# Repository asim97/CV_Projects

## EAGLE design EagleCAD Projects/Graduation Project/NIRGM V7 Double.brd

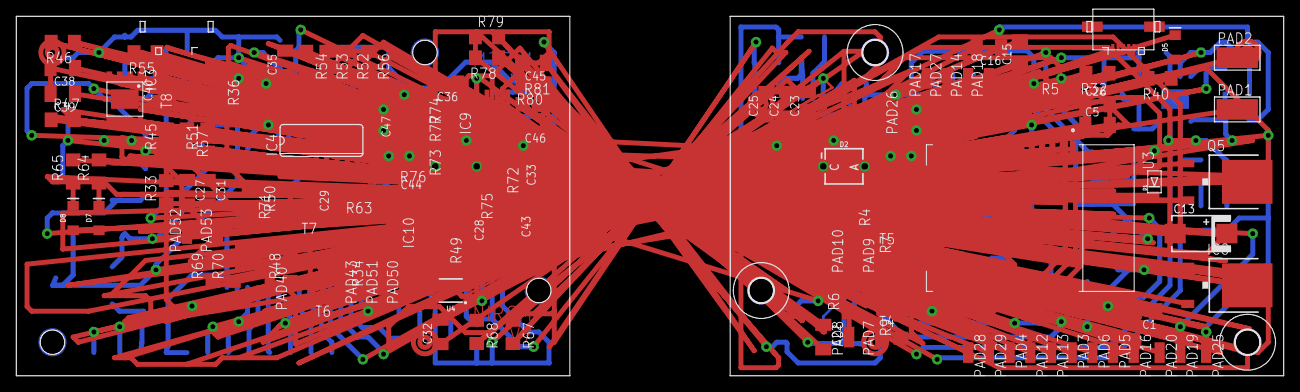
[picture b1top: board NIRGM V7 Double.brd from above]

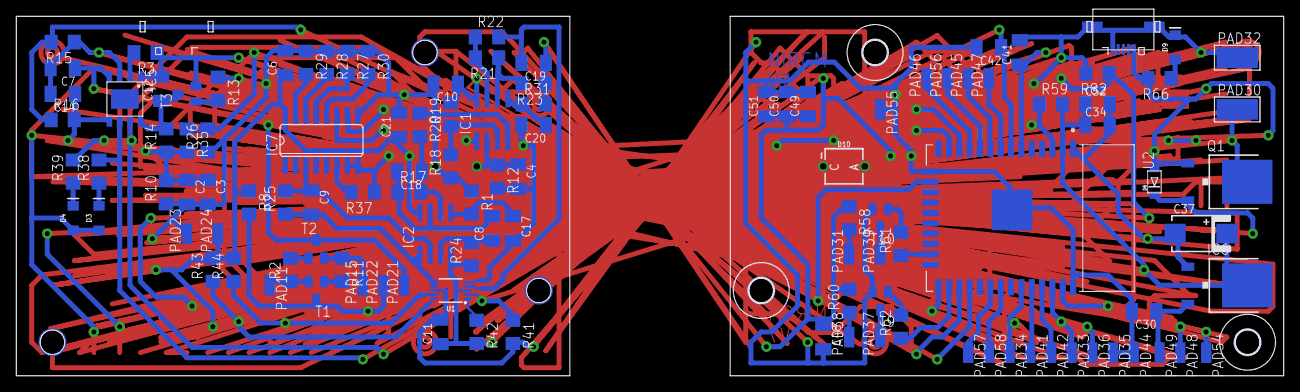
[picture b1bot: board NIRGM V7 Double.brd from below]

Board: 2 copper layers, 155.6 x 44.1 mm, 236 parts (118 on the bottom side), 126 nets.

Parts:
C1, C3, C7, C8, C12, C14, C17, C24, C25, C28, C30, C31, C38, C39, C40, C43, C50, C51: 10uf; C1206K
C2, C5, C6, C9, C10, C15, C16, C18, C21, C22, C23, C26, C27, C29, C34, C35, C36, C41, C42, C44, C47, C48, C49, C52: 100nf; C1206K
C4, C33: 5.7pf; C1206K
C11, C32: 1uf; C1206K
C13, C37: 220uf; 7343/T
C19, C45: 100nF; C1206K
C20, C46: 1uF; C1206K
D1, D6: SOD4007; SOD-123FL
D2, D10: BPW34
D3, D7: GREEN; LED-1206
D4, D5, D8, D9: RED; LED-1206
H1, H2, H3, H4, H5, H6: MOUNT-HOLE3.0; 3,0
IC1, IC2, IC9, IC10: MCP602SN; SO08
IC3, IC5: TP4056; SOP-8
IC4, IC7: 4051D; SO16
IC6, IC8: 3.3v; TO252
PAD1, PAD2, PAD30, PAD32: 5-2,5
PAD3, PAD4, PAD5, PAD6, PAD7, PAD8, PAD9, PAD10, PAD11, PAD12, PAD13, PAD14, PAD15, PAD16, PAD17, PAD18, PAD19, PAD20, PAD21, PAD22, PAD23, PAD24, PAD25, PAD26, PAD27, PAD28, PAD29, PAD31, PAD33, PAD34, PAD35, PAD36, PAD37, PAD38, PAD39, PAD40, PAD41, PAD42, PAD43, PAD44, PAD45, PAD46, PAD47, PAD48, PAD49, PAD50, PAD51, PAD52, PAD53, PAD54, PAD55, PAD56, PAD57, PAD58: SMD1,27-2,54
Q1, Q5: ME12P04; TO252
R1, R17, R18, R19, R73, R74, R75, R76: 100k; R1206
R2, R8, R10, R11, R14, R20, R24, R29, R33, R34, R37, R41, R42, R43, R44, R45, R48, R49, R54, R63, R67, R68, R69, R70, R71, R77: 10k; R1206
R3, R55: 2.2k; R1206
R4, R6, R58, R60: 20R; R1206
R5, R28, R32, R53, R59, R82: 4.7k; R1206
R7, R9, R13, R23, R27, R36, R38, R39, R40, R52, R61, R62, R64, R65, R66, R80: 1k; R1206
R12, R72: 1M; R1206
R15, R16, R26, R30, R35, R46, R47, R51, R56, R57: 47k; R1206
R21, R78: 57k; R1206
R22, R79: 200k; R1206
R25, R50: 220k; R1206
R31, R81: 2.2M; R1206
T1, T2, T3, T4, T5, T6, T7, T8, T9, T10: BC850; SOT23
U1, U4: ADS1015; MSOP10
U2, U3: ESP32-WROOM-32D; MODULE_ESP32-WROOM-32D
U$1, U$2: MICRO-USB; 47589-0001

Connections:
3.3V: C5.1, C6.1, C10.1, C11.2, C13.+, C21.1, C22.1, C23.1, C24.1, C25.1, C26.1, IC1.8, IC2.8, IC7.16, IC8.3, PAD6.1, PAD24.1, R4.1, R5.2, R6.2, R8.1, R19.2, R41.2, R43.2, R44.2, U1.8, U3.2
3.3V1: C32.2, C34.1, C35.1, C36.1, C37.+, C47.1, C48.1, C49.1, C50.1, C51.1, C52.1, IC4.16, IC6.3, IC9.8, IC10.8, PAD36.1, PAD53.1, R58.1, R59.2, R60.2, R67.2, R69.2, R70.2, R71.1, R74.2, U2.2, U4.8
ADS_COMP: R41.1, U1.2, U3.16
ADS_COMP1: R67.1, U2.16, U4.2
CHARGED_LOW: IC5.6, R38.2, U3.28
CHARGED_LOW1: IC3.6, R64.2, U2.28
CHARGE_DISABLE: R13.1, R32.1, U3.37
CHARGE_DISABLE1: R36.1, R82.1, U2.37
CHARGE_E: C12.1, IC5.8, R14.2, T3.3
CHARGE_E1: C40.1, IC3.8, R45.2, T8.3
CHARGING_LOW: IC5.7, R39.2, U3.27
CHARGING_LOW1: IC3.7, R65.2, U2.27
CHP_EN: PAD21.1, R5.1, T2.3, U3.3
CHP_EN1: PAD50.1, R59.1, T7.3, U2.3
CH_RX: PAD12.1, U3.34
CH_RX1: PAD41.1, U2.34
CH_TX: PAD13.1, U3.35
CH_TX1: PAD42.1, U2.35
DTR: PAD11.1, R2.1, T1.2
DTR1: PAD40.1, R48.1, T6.2
EN_IR1: R9.1, U3.26
EN_IR2: R7.1, U3.23
EN_IR3: R62.1, U2.26
EN_IR4: R61.1, U2.23
GND: C1.2, C2.2, C3.2, C5.2, C6.2, C7.2, C10.2, C11.1, C12.2, C13.-, C14.2, C15.2, C16.2, C19.1, C21.2, C22.2, C23.2, C24.2, C25.2, C26.2, D2.P$1, D5.C, IC1.4, IC2.4, IC5.1, IC5.3, IC7.7, IC7.8, IC7.9, IC8.1, PAD2.1, PAD5.1, PAD16.1, PAD23.1, PAD26.1, R1.1, R3.1, R10.1, R15.1, R18.1, R20.1, R23.1, R24.1, R26.1, R27.1, R28.1, R29.1, R30.1, R31.2, R32.2, R37.1, R42.2, T3.2, T4.2, T5.2, U1.3, U3.1, U3.15, U3.38, U3.39, U$1.5
GND1: C27.2, C30.2, C31.2, C32.1, C34.2, C35.2, C36.2, C37.-, C38.2, C39.2, C40.2, C41.2, C42.2, C45.1, C47.2, C48.2, C49.2, C50.2, C51.2, C52.2, D9.C, D10.P$1, IC3.1, IC3.3, IC4.7, IC4.8, IC4.9, IC6.1, IC9.4, IC10.4, PAD32.1, PAD35.1, PAD44.1, PAD52.1, PAD55.1, R33.1, R46.1, R49.1, R51.1, R52.1, R53.1, R54.1, R55.1, R56.1, R63.1, R68.2, R73.1, R75.1, R77.1, R80.1, R81.2, R82.2, T8.2, T9.2, T10.2, U2.1, U2.15, U2.38, U2.39, U4.3, U$2.5
IO0: PAD22.1, R8.2, T1.3, U3.25
IO1: PAD47.1, U2.8
IO2: PAD45.1, U2.9
IO3: PAD51.1, R71.2, T6.3, U2.25
IO4: PAD46.1, U2.11
IO5: PAD58.1, U2.31
IO6: PAD57.1, U2.30
IO7: PAD56.1, U2.10
IO18: PAD28.1, U3.30
IO19: PAD29.1, U3.31
IO25: PAD27.1, U3.10
IO26: PAD17.1, U3.11
IO32: PAD18.1, U3.8
IO33: PAD14.1, U3.9
IR1_LED_ANODE: PAD8.1, R6.1
IR1_LED_ANODE1: PAD38.1, R60.1
IR1_LED_CATHODE: PAD7.1, T4.3
IR1_LED_CATHODE1: PAD37.1, T9.3
IR2_LED_ANODE: PAD10.1, R4.2
IR2_LED_ANODE1: PAD31.1, R58.2
IR2_LED_CATHODE: PAD9.1, T5.3
IR2_LED_CATHODE1: PAD39.1, T10.3
unnamed: D5.A, R40.1
unnamed: D4.C, R39.1
unnamed: R7.2, T5.1
unnamed: D3.C, R38.1
unnamed: R11.2, T1.1
unnamed: C17.1, IC2.5, R1.2
unnamed: C4.1, D2.P$2, IC1.2, R12.1
unnamed: R9.2, T4.1
unnamed: R42.1, U1.1
unnamed: IC1.3, R18.2, R19.1
unnamed: IC7.6, R37.2
unnamed: C8.2, C18.2, IC2.7, R17.1
unnamed: R13.2, T3.1
unnamed: C18.1, IC2.6, R17.2, R20.2
unnamed: IC1.6, R21.1, R23.2
unnamed: C20.1, IC1.5, R31.1
unnamed: IC1.7, R21.2, R22.1
unnamed: R2.2, T2.1
unnamed: R36.2, T8.1
unnamed: R34.2, T6.1
unnamed: R48.2, T7.1
unnamed: C28.1, IC10.3, R49.2
unnamed: C29.1, IC4.3, IC10.2, R50.2
unnamed: IC4.13, R52.2
unnamed: IC4.14, R53.2
unnamed: IC4.15, R54.2
unnamed: C8.1, IC2.3, R24.2
unnamed: IC4.12, R56.2
unnamed: IC4.6, R63.2
unnamed: D9.A, R66.1
unnamed: R68.1, U4.1
unnamed: R62.2, T9.1
unnamed: R61.2, T10.1
unnamed: C33.1, D10.P$2, IC9.2, R72.1
unnamed: IC9.3, R73.2, R74.1
unnamed: D8.C, R65.1
unnamed: C9.1, IC2.2, IC7.3, R25.2
unnamed: IC7.13, R27.2
unnamed: IC7.14, R28.2
unnamed: IC7.15, R29.2
unnamed: IC7.12, R30.2
unnamed: D7.C, R64.1
unnamed: C43.1, IC10.5, R75.2
unnamed: C28.2, C44.2, IC10.7, R76.1
unnamed: C44.1, IC10.6, R76.2, R77.2
unnamed: IC9.6, R78.1, R80.2
unnamed: C46.1, IC9.5, R81.1
unnamed: IC9.7, R78.2, R79.1
PHOTODIODE_ADC: C4.2, C17.2, C20.2, IC1.1, R12.2, U1.5
PHOTODIODE_ADC1: C33.2, C43.2, C46.2, IC9.1, R72.2, U4.5
PPG_SIGNAL_1_ADC: C9.2, IC2.1, R25.1, U1.6, U1.7
PPG_SIGNAL_1_ADC1: C29.2, IC10.1, R50.1, U4.6, U4.7
PPG_SIGNAL_2_ADC: C19.2, R22.2, U1.4
PPG_SIGNAL_2_ADC1: C45.2, R79.2, U4.4
PPG_SIGNAL_GAIN_A: IC7.11, U3.13
PPG_SIGNAL_GAIN_A1: IC4.11, U2.13
PPG_SIGNAL_GAIN_B: IC7.10, U3.12
PPG_SIGNAL_GAIN_B1: IC4.10, U2.12
RTS: PAD15.1, R11.1, T2.2
RTS1: PAD43.1, R34.1, T7.2
R_PROG: IC5.2, R3.2
R_PROG1: IC3.2, R55.2
SCL: PAD3.1, R43.1, U1.10, U3.36
SCL1: PAD33.1, R69.1, U2.36, U4.10
SDA: PAD4.1, R44.1, U1.9, U3.33
SDA1: PAD34.1, R70.1, U2.33, U4.9
VIN: C1.1, IC8.2, PAD20.1
VIN1: C30.1, IC6.2, PAD49.1
VIN_SW: D1.C, PAD19.1, Q5.2
VIN_SW1: D6.C, PAD48.1, Q1.2
V_BATT: C14.1, IC5.5, PAD1.1, Q5.3, R16.2
V_BATT1: C39.1, IC3.5, PAD30.1, Q1.3, R47.2
V_BATT_ADC: C16.1, R15.2, R16.1, U3.7
V_BATT_ADC1: C42.1, R46.2, R47.1, U2.7
V_USB: C2.1, C3.1, C7.1, D1.A, D3.A, D4.A, IC5.4, PAD25.1, Q5.1, R10.2, R14.1, R35.2, R40.2, U$1.1
V_USB1: C27.1, C31.1, C38.1, D6.A, D7.A, D8.A, IC3.4, PAD54.1, Q1.1, R33.2, R45.1, R57.2, R66.2, U$2.1
V_USB_ADC: C15.1, R26.2, R35.1, U3.6
V_USB_ADC1: C41.1, R51.2, R57.1, U2.6

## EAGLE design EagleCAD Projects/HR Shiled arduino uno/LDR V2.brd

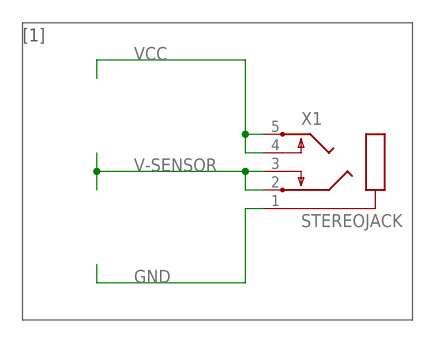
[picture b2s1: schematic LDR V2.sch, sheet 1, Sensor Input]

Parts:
X1: STEREOJACK; STX3100

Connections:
GND: X1.1; also elsewhere on the board
V-SENSOR: X1.2, X1.3; also elsewhere on the board
VCC: X1.4, X1.5; also elsewhere on the board

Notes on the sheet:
[1]

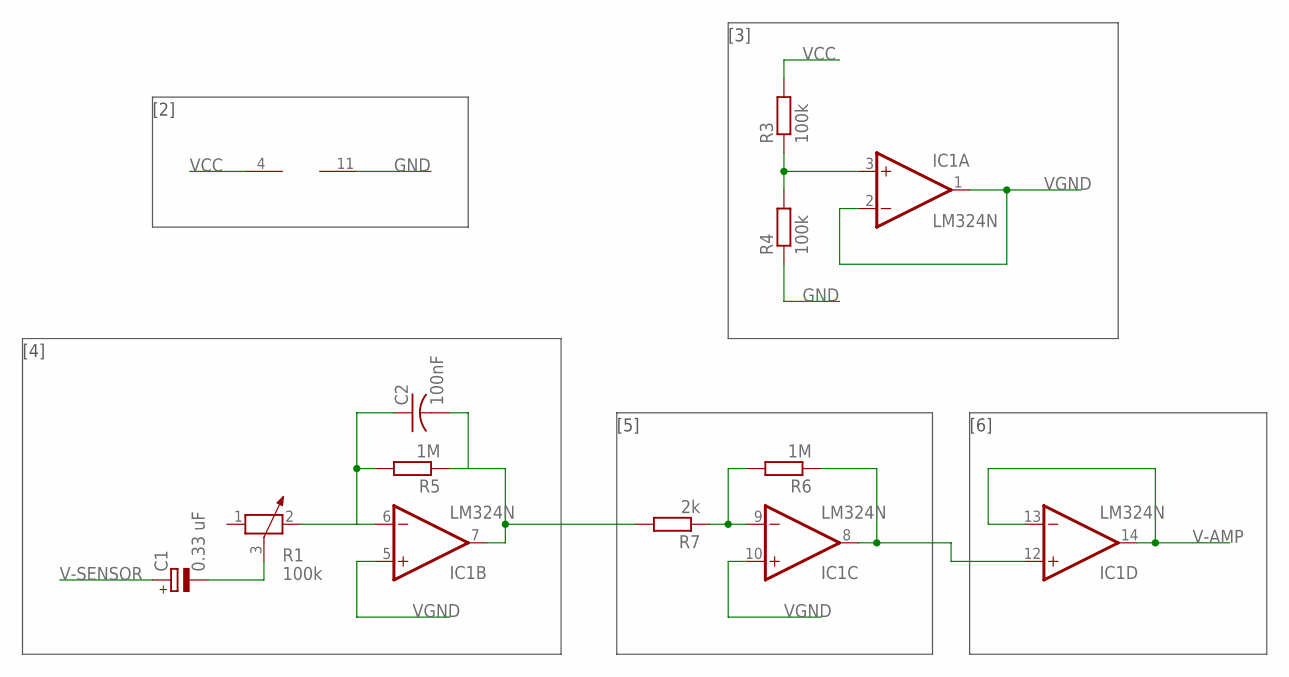
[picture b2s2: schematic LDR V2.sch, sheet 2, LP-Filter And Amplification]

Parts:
C1: 0.33 uF; E1,8-4
C2: 100nF; C025-025X050
IC1: LM324N; DIL14
R1: 100k; PT-10
R3, R4: 100k; 0207/7
R5, R6: 1M; 0207/7
R7: 2k; 0207/7

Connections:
GND: IC1.11 (V-), R4.1; also elsewhere on the board
unnamed: C1.-, R1.3
unnamed: C2.1, IC1.6 (-IN), R1.2, R5.2
unnamed: IC1.3 (+IN), R3.1, R4.2
unnamed: C2.2, IC1.7 (OUT), R5.1, R7.2
unnamed: IC1.9 (-IN), R6.2, R7.1
unnamed: IC1.8 (OUT), IC1.12 (+IN), R6.1
V-AMP: IC1.13 (-IN), IC1.14 (OUT); also elsewhere on the board
V-SENSOR: C1.+; also elsewhere on the board
VCC: IC1.4 (V+), R3.2; also elsewhere on the board
VGND: IC1.1 (OUT), IC1.2 (-IN), IC1.5 (+IN), IC1.10 (+IN)

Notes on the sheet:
[3]
[2]
[4]
[5]
[6]

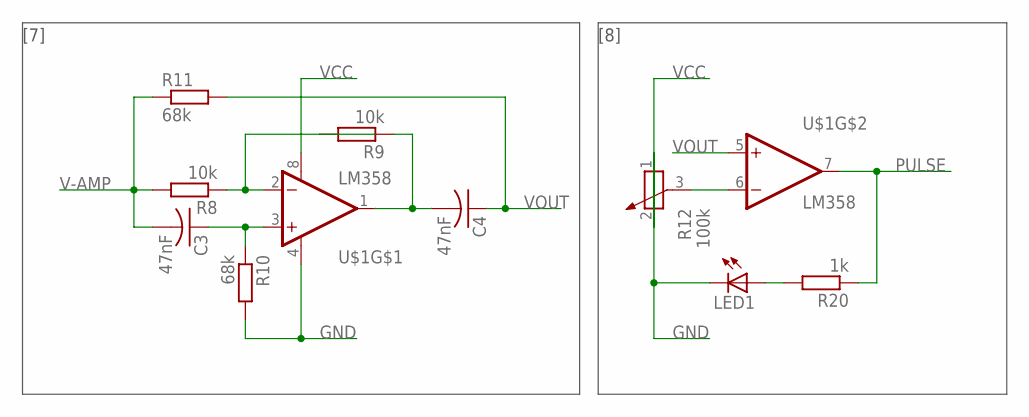
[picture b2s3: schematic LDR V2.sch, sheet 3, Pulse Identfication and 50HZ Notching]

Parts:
C3, C4: 47nF; C025-025X050
LED1: LED5MM
R8, R9: 10k; 0207/7
R10, R11: 68k; 0207/7
R12: 100k; PT-10
R20: 1k; 0207/7
U$1: LM358; DIP08

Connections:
GND: LED1.K (C), R10.2, R12.1, U$1.4 (V-); also elsewhere on the board
unnamed: R8.1, R9.2, U$1.2 (-IN)
unnamed: C3.1, R10.1, U$1.3 (+IN)
unnamed: R12.3, U$1.6 (-IN)
unnamed: C4.2, R9.1, U$1.1 (OUT)
unnamed: LED1.A, R20.2
PULSE: R20.1, U$1.7 (OUT); also elsewhere on the board
V-AMP: C3.2, R8.2, R11.1; also elsewhere on the board
VCC: R12.2, U$1.8 (V+); also elsewhere on the board
VOUT: C4.1, R11.2, U$1.5 (+IN); also elsewhere on the board

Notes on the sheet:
[7]
[8]

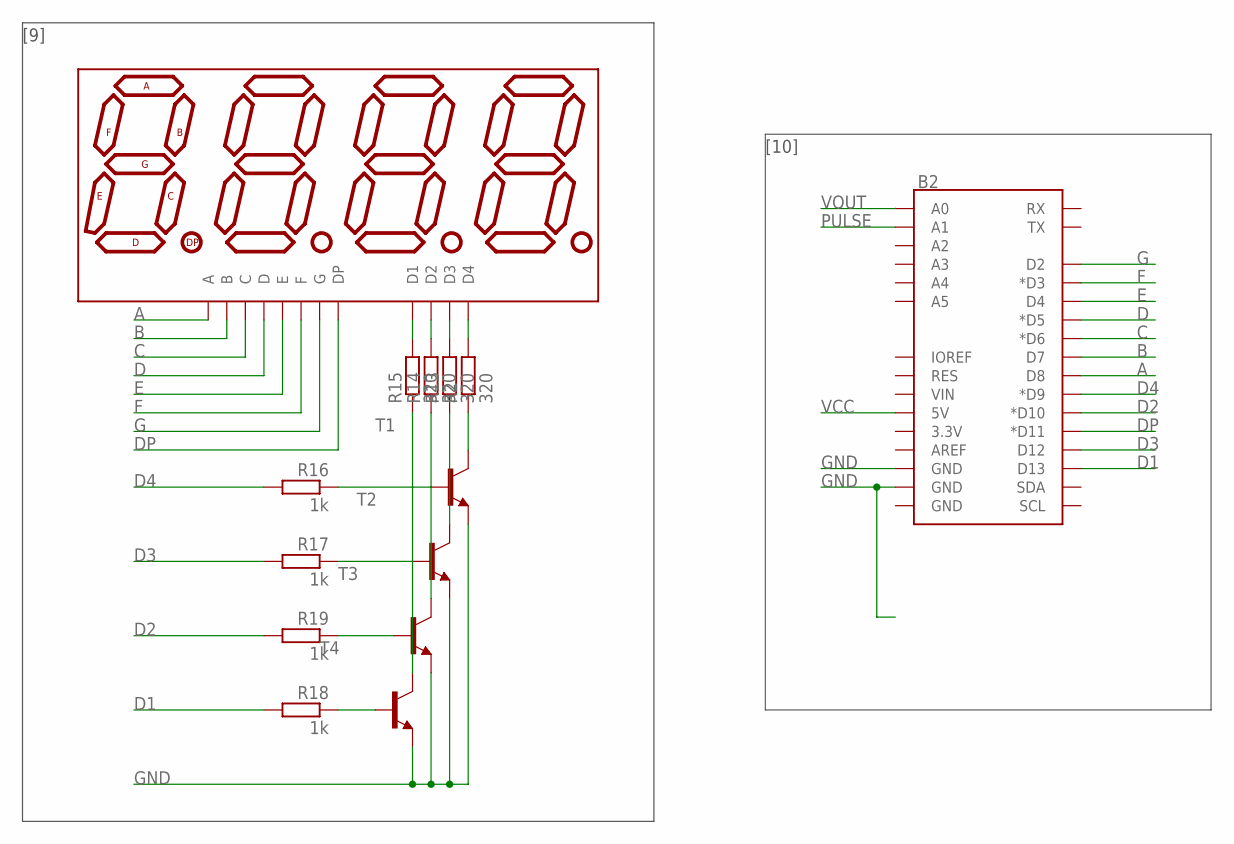
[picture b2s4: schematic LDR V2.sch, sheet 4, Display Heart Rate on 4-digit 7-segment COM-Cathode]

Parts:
B2: ARDUINO_UNO_R3_SHIELDUNO_R3_SHIELD_LOCK; UNO_R3_SHIELD_LOCK
DISP2: ATA8041AB; 7-SEGMENT-4DIGIT-20MM
R2, R13, R14, R15: 320; 0207/7
R16, R17, R18, R19: 1k; 0207/7
T1, T2, T3, T4: 2N2222-NPN-TO92-EBC; TO92-EBC

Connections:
1: DISP2.12 (D1), R15.2
2: DISP2.9 (D2), R14.2
3: DISP2.8 (D3), R13.2
4: DISP2.6 (D4), R2.2
A: B2.D8, DISP2.11 (A)
B: B2.D7, DISP2.7 (B)
C: B2.D6 (*D6), DISP2.4 (C)
D: B2.D5 (*D5), DISP2.2 (D)
D1: B2.D13, R18.2
D2: B2.D10 (*D10), R19.2
D3: B2.D12, R17.2
D4: B2.D9 (*D9), R16.2
DP: B2.D11 (*D11), DISP2.3 (DP)
E: B2.D4, DISP2.1 (E)
F: B2.D3 (*D3), DISP2.10 (F)
G: B2.D2, DISP2.5 (G)
GND: B2.GND@1 (GND), B2.GND@2 (GND), T1.E, T2.E, T3.E, T4.E; also elsewhere on the board
unnamed: R2.1, T1.C
unnamed: R18.1, T4.B
unnamed: R19.1, T3.B
unnamed: R17.1, T2.B
unnamed: R16.1, T1.B
unnamed: R13.1, T2.C
unnamed: R14.1, T3.C
unnamed: R15.1, T4.C
PULSE: B2.A1; also elsewhere on the board
VCC: B2.5V; also elsewhere on the board
VOUT: B2.A0; also elsewhere on the board

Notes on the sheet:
[9]
[10]

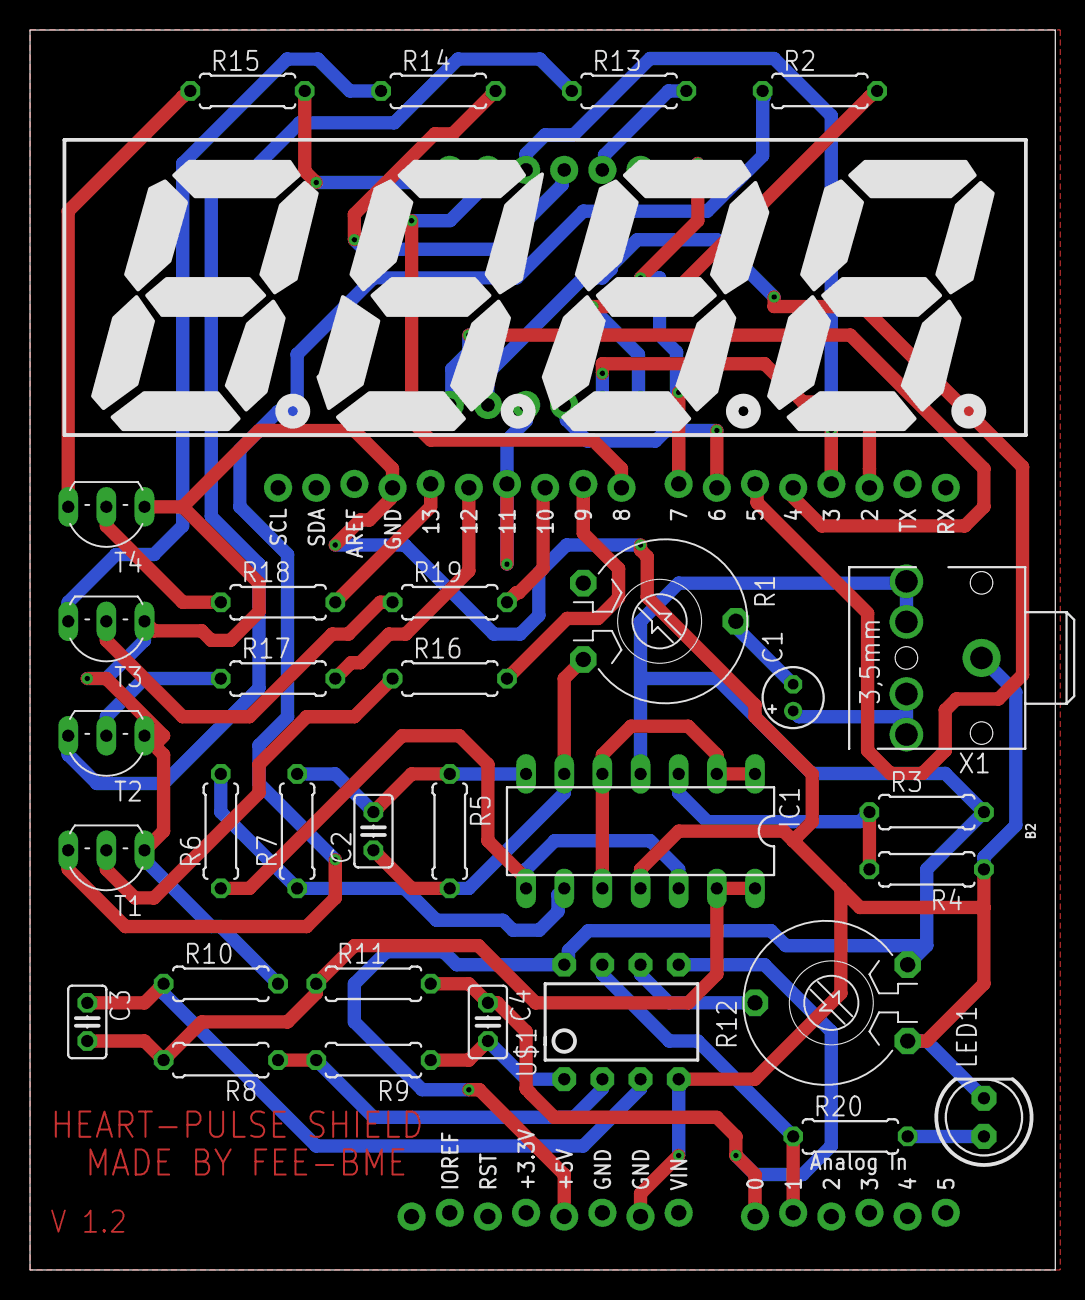
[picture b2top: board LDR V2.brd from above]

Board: 2 copper layers, 68.2 x 82.5 mm, 34 parts (0 on the bottom side), 42 nets.

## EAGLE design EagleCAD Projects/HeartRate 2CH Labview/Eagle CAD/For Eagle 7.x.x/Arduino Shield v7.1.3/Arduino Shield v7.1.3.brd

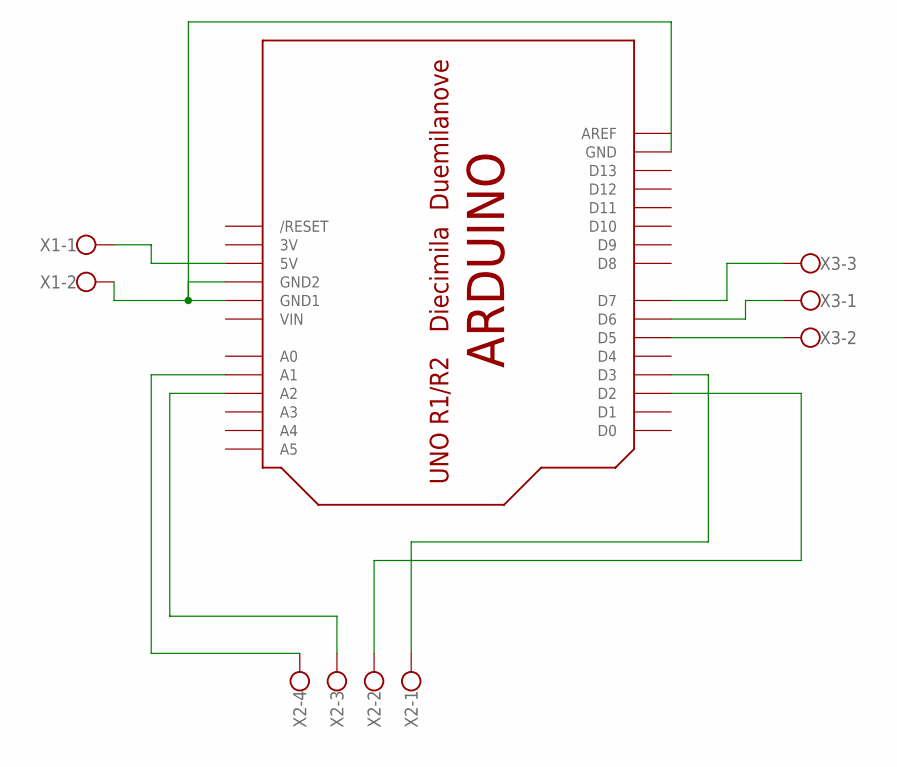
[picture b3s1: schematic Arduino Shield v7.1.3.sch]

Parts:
U$1: ARDUINOUNO; ARDUINO
X1: W237-102
X2: W237-4
X3: W237-103

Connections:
3V: U$1.3V
GND: U$1.GND, U$1.GND1, U$1.GND2, X1.2
unnamed: U$1.A1, X2.4
unnamed: U$1.A2, X2.3
unnamed: U$1.D3, X2.1
unnamed: U$1.D5, X3.2
unnamed: U$1.D6, X3.1
unnamed: U$1.D7, X3.3
unnamed: U$1.D2, X2.2
unnamed: U$1.5V, X1.1
VIN: U$1.VIN

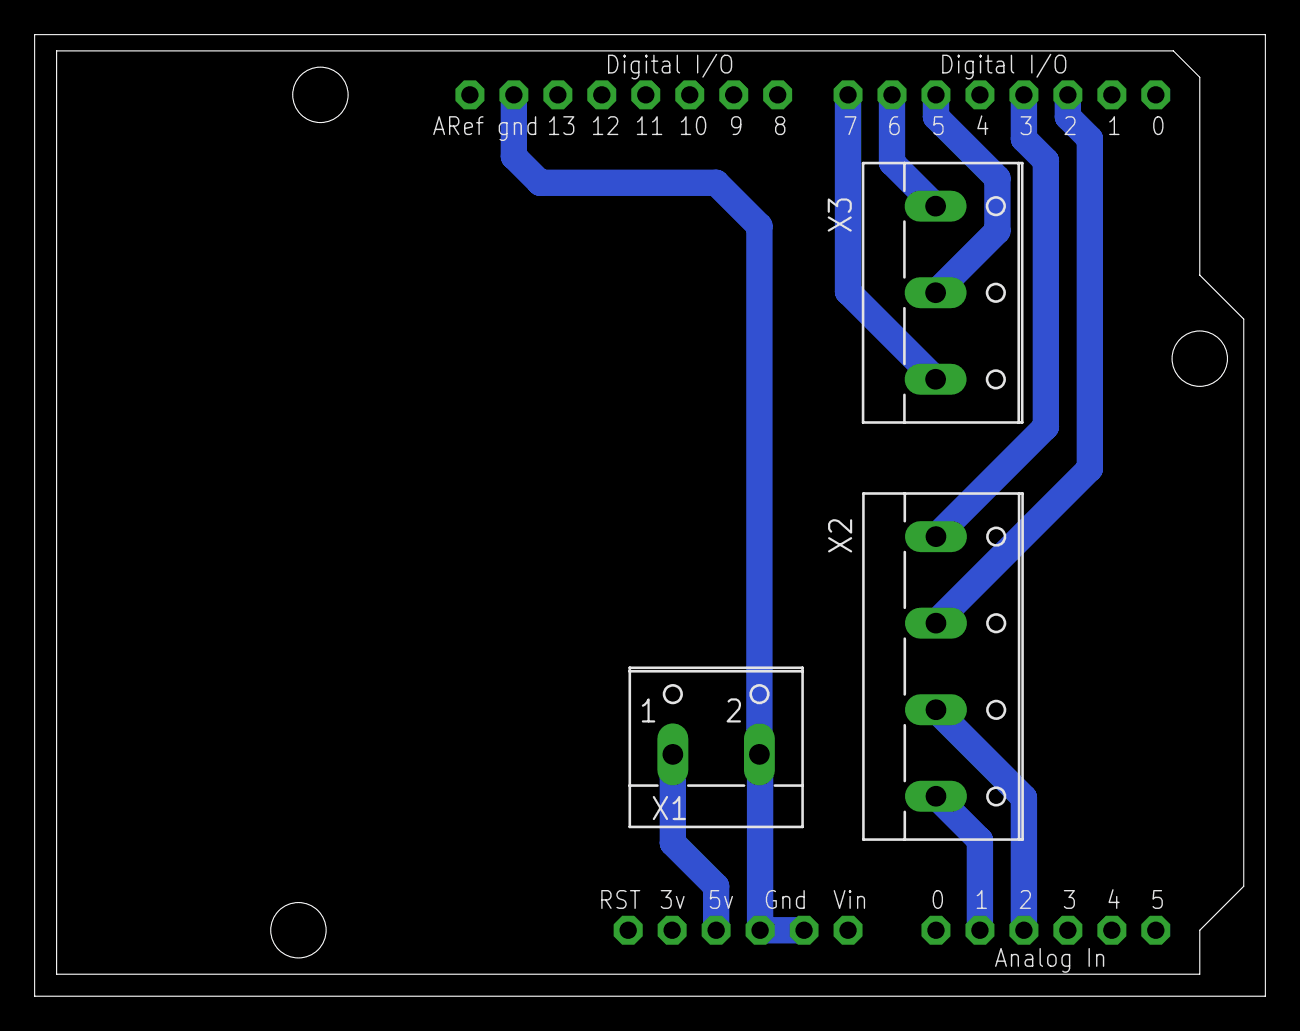
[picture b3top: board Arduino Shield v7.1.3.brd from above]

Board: 2 copper layers, 71.1 x 55.6 mm, 4 parts (0 on the bottom side), 9 nets.

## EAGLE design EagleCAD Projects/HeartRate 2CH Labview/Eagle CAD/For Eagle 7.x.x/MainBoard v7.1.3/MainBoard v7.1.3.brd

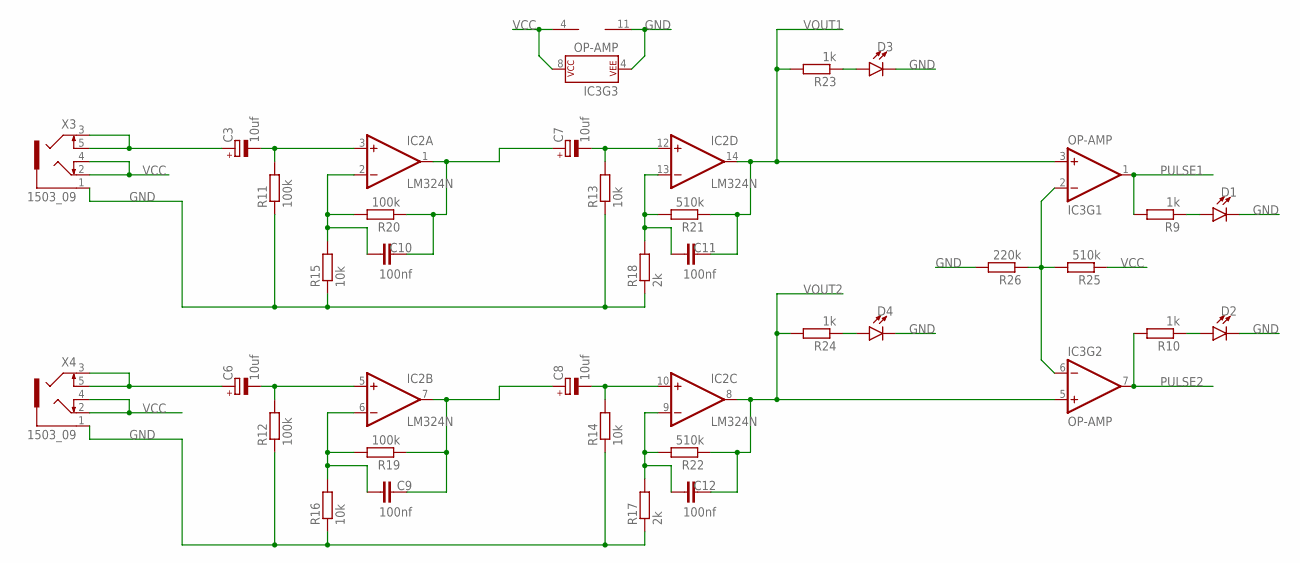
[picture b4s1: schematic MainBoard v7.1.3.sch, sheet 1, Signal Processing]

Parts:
C3, C6, C7, C8: 10uf; E2-5
C9, C10, C11, C12: 100nf; C050-030X075
D1, D2, D3, D4: LED5MM; LED_5MM
IC2: LM324N; DIL14
IC3: OP-AMP; DIP08
R9, R10, R23, R24: 1k; 0207/10
R11, R12, R19, R20: 100k; 0207/10
R13, R14, R15, R16: 10k; 0207/10
R17, R18: 2k; 0207/10
R21, R22, R25: 510k; 0207/10
R26: 220k; 0207/10
X3, X4: 1503_09

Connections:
GND: D1.K (C), D2.K (C), D3.K (C), D4.K (C), IC2.11 (V-), IC3.4 (P$V-), R11.1, R12.1, R13.1, R14.1, R15.1, R16.1, R17.1, R18.1, R26.2, X3.1, X4.1; also elsewhere on the board
unnamed: C8.+, C9.2, IC2.7 (OUT), R19.1
unnamed: C9.1, IC2.6 (-IN), R16.2, R19.2
unnamed: D1.A, R9.1
unnamed: C7.+, C10.2, IC2.1 (OUT), R20.1
unnamed: C10.1, IC2.2 (-IN), R15.2, R20.2
unnamed: C11.1, IC2.13 (-IN), R18.2, R21.2
unnamed: IC3.2 (-IN), IC3.6 (-IN), R25.2, R26.1
unnamed: C12.1, IC2.9 (-IN), R17.2, R22.2
unnamed: C6.+, X4.3, X4.5
unnamed: D2.A, R10.1
unnamed: C3.+, X3.3, X3.5
unnamed: C6.-, IC2.5 (+IN), R12.2
unnamed: C7.-, IC2.12 (+IN), R13.2
unnamed: C8.-, IC2.10 (+IN), R14.2
unnamed: C3.-, IC2.3 (+IN), R11.2
unnamed: D3.A, R23.1
unnamed: D4.A, R24.1
PULSE1: IC3.1 (OUT), R9.2; also elsewhere on the board
PULSE2: IC3.7 (OUT), R10.2; also elsewhere on the board
VCC: IC2.4 (V+), IC3.8 (P$V+), R25.1, X3.2, X3.4, X4.2, X4.4; also elsewhere on the board
VOUT1: C11.2, IC2.14 (OUT), IC3.3 (+IN), R21.1, R23.2; also elsewhere on the board
VOUT2: C12.2, IC2.8 (OUT), IC3.5 (+IN), R22.1, R24.2; also elsewhere on the board

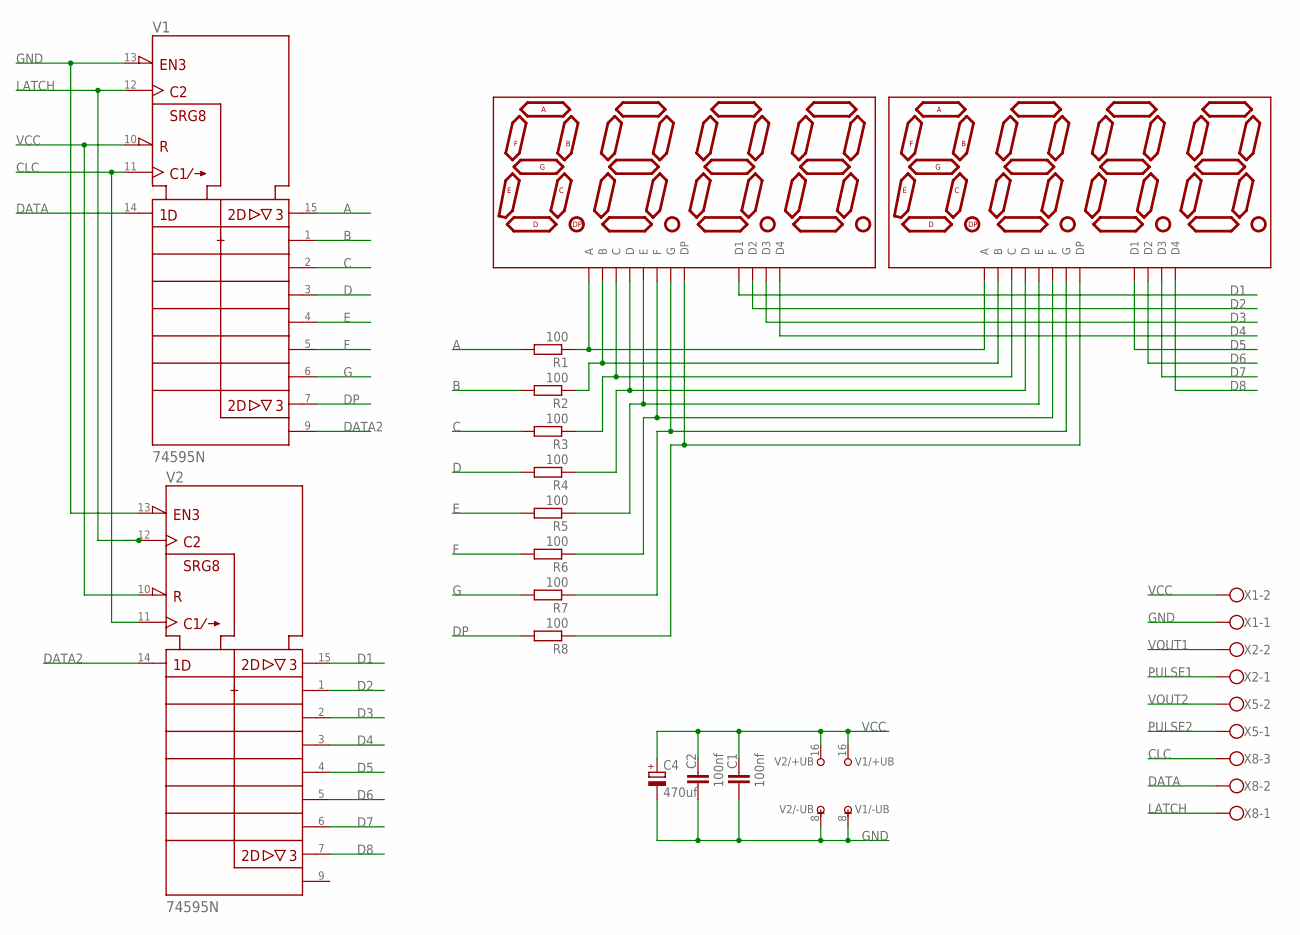
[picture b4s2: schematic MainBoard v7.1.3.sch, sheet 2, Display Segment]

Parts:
C1, C2: 100nf; C050-030X075
C4: 470uf; E3,5-8
DISP1, DISP2: ATA8041AB; 7-SEGMENT-4DIGIT-20MM
R1, R2, R3, R4, R5, R6, R7, R8: 100; 0207/10
V1, V2: 74595N; DIL16
X1, X2, X5: W237-102
X8: W237-103

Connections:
A: R1.2, V1.15 (QA)
B: R2.2, V1.1 (QB)
C: R3.2, V1.2 (QC)
CLC: V1.11 (SRCK), V2.11 (SRCK), X8.3
D: R4.2, V1.3 (QD)
D1: DISP2.12 (D1), V2.15 (QA)
D2: DISP2.9 (D2), V2.1 (QB)
D3: DISP2.8 (D3), V2.2 (QC)
D4: DISP2.6 (D4), V2.3 (QD)
D5: DISP1.12 (D1), V2.4 (QE)
D6: DISP1.9 (D2), V2.5 (QF)
D7: DISP1.8 (D3), V2.6 (QG)
D8: DISP1.6 (D4), V2.7 (QH)
DATA: V1.14 (SER), X8.2
DATA2: V1.9 (QH*), V2.14 (SER)
DP: R8.2, V1.7 (QH)
E: R5.2, V1.4 (QE)
F: R6.2, V1.5 (QF)
G: R7.2, V1.6 (QG)
GND: C1.1, C2.1, C4.-, V1.8 (-UB), V1.13 (!G), V2.8 (-UB), V2.13 (!G), X1.1; also elsewhere on the board
LATCH: V1.12 (RCK), V2.12 (RCK), X8.1
unnamed: DISP1.11 (A), DISP2.11 (A), R1.1
unnamed: DISP1.7 (B), DISP2.7 (B), R2.1
unnamed: DISP1.4 (C), DISP2.4 (C), R3.1
unnamed: DISP1.2 (D), DISP2.2 (D), R4.1
unnamed: DISP1.1 (E), DISP2.1 (E), R5.1
unnamed: DISP1.10 (F), DISP2.10 (F), R6.1
unnamed: DISP1.5 (G), DISP2.5 (G), R7.1
unnamed: DISP1.3 (DP), DISP2.3 (DP), R8.1
PULSE1: X2.1; also elsewhere on the board
PULSE2: X5.1; also elsewhere on the board
VCC: C1.2, C2.2, C4.+, V1.10 (!SRCLR), V1.16 (+UB), V2.10 (!SRCLR), V2.16 (+UB), X1.2; also elsewhere on the board
VOUT1: X2.2; also elsewhere on the board
VOUT2: X5.2; also elsewhere on the board

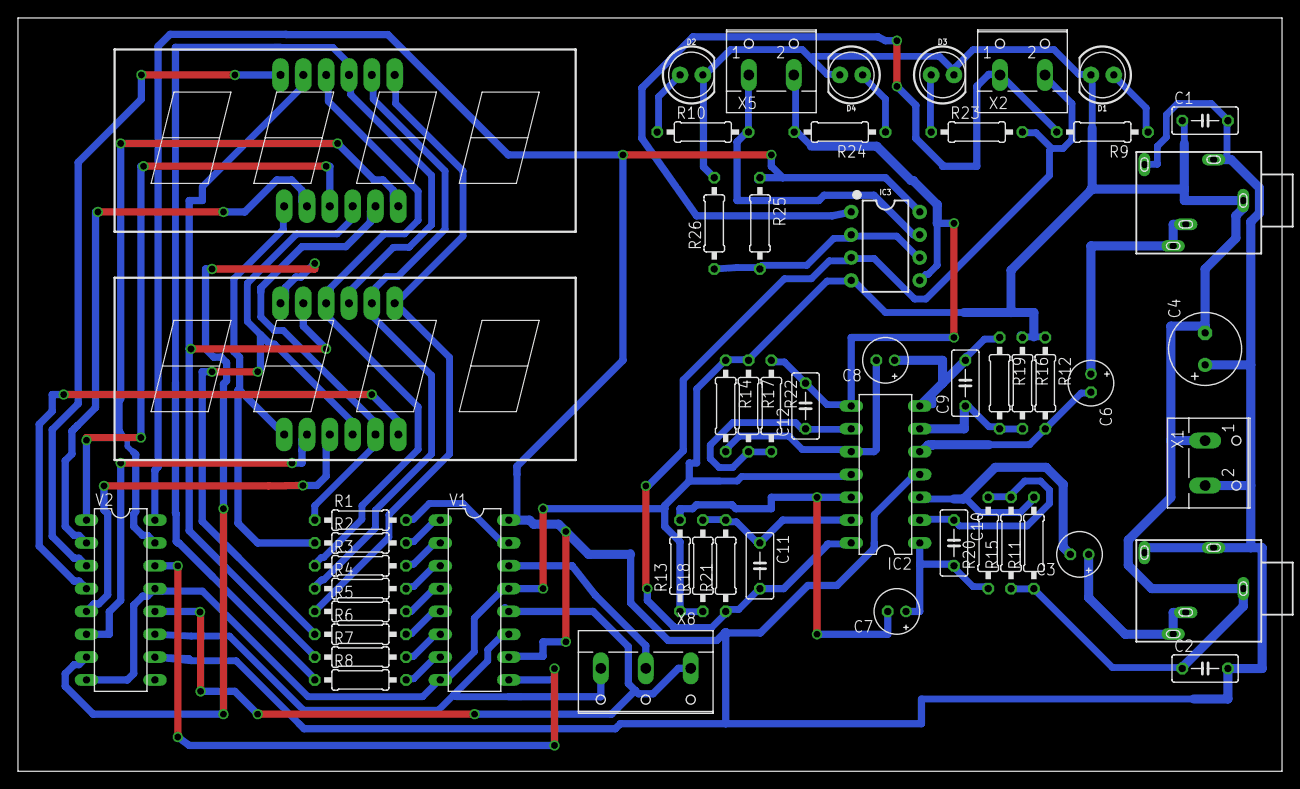
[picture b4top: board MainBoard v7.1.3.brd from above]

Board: 2 copper layers, 140.6 x 83.8 mm, 53 parts (0 on the bottom side), 51 nets.

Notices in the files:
parts and their libraries:
SparkFun-Sensors: Licensing: Creative Commons ShareAlike 4.0 International - https://creativecommons.org/licenses/by-sa/4.0
con-molex-usb: (C) 2014 Tomasz Boleslaw CEDRO, cederom@tlen.pl, http://www.tomek.cedro.info.
